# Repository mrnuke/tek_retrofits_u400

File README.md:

# Tektronix U400 channel switch retrofit
Replacement for the Tektronix 155-0236-00 (U400) channel switch hybrid module from 2400 series scopes

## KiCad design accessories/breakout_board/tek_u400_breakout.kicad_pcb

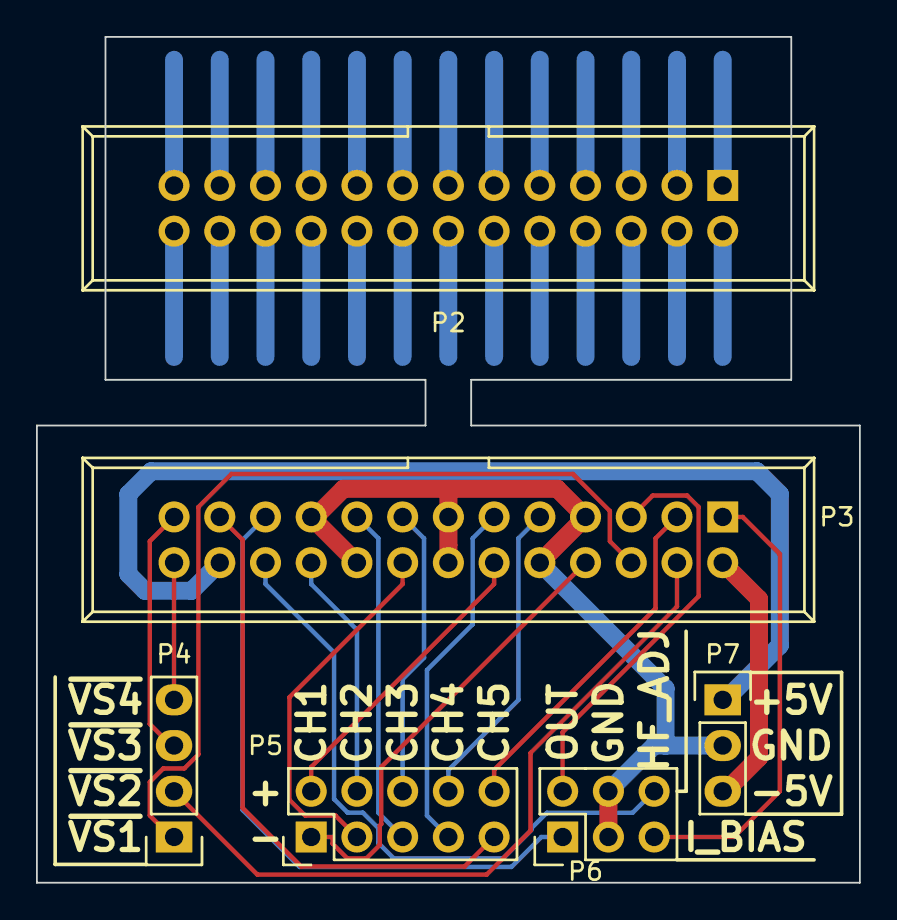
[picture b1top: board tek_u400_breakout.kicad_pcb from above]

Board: 2 copper layers, 45.7 x 47.0 mm, 7 parts (0 on the bottom side), 47 nets.

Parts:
P1: DIL_26_PINS; Tek-DIL-26
P2: CONN_02X13; IDC_Header_Straight_26pins
P3: DIL_26_PINS; IDC_Header_Straight_26pins
P4: CONN_01X04; Pin_Header_Straight_1x04
P5: CONN_02X05; Pin_Header_Straight_2x05
P6: CONN_02X03; Pin_Header_Straight_2x03
P7: CONN_01X03; Pin_Header_Straight_1x03

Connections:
/CH_1+: P3.8, P5.1
/CH_1-: P3.12, P5.2
/CH_2+: P3.16, P5.3
/CH_2-: P3.20, P5.4
/CH_3+: P3.17, P5.5
/CH_3-: P3.15, P5.6
/CH_4+: P3.11, P5.7
/CH_4-: P3.9, P5.8
/CH_5+: P3.23, P5.9
/CH_5-: P3.3, P5.10
/HF_ADJ: P3.22, P6.6
/I_BIAS: P3.1, P6.5
/OUT+: P3.21, P6.1
/OUT-: P3.5, P6.2
/~VS1: P3.6, P4.1
/~VS2: P3.4, P4.2
/~VS3: P3.25, P4.3
/~VS4: P3.26, P4.4
GND: P3.7, P3.10, P3.13, P3.14, P3.18, P3.19, P6.3, P6.4, P7.2
unnamed: P1.1, P2.1
unnamed: P1.2, P2.3
unnamed: P1.3, P2.5
unnamed: P1.4, P2.7
unnamed: P1.5, P2.9
unnamed: P1.6, P2.11
unnamed: P1.7, P2.13
unnamed: P1.8, P2.15
unnamed: P1.9, P2.17
unnamed: P1.10, P2.19
unnamed: P1.11, P2.21
unnamed: P1.12, P2.23
unnamed: P1.13, P2.25
unnamed: P1.14, P2.26
unnamed: P1.15, P2.24
unnamed: P1.16, P2.22
unnamed: P1.17, P2.20
unnamed: P1.18, P2.18
unnamed: P1.19, P2.16
unnamed: P1.20, P2.14
unnamed: P1.21, P2.12
unnamed: P1.22, P2.10
unnamed: P1.23, P2.8
unnamed: P1.24, P2.6
unnamed: P1.25, P2.4
unnamed: P1.26, P2.2
VCC: P3.24, P7.1
VEE: P3.2, P7.3

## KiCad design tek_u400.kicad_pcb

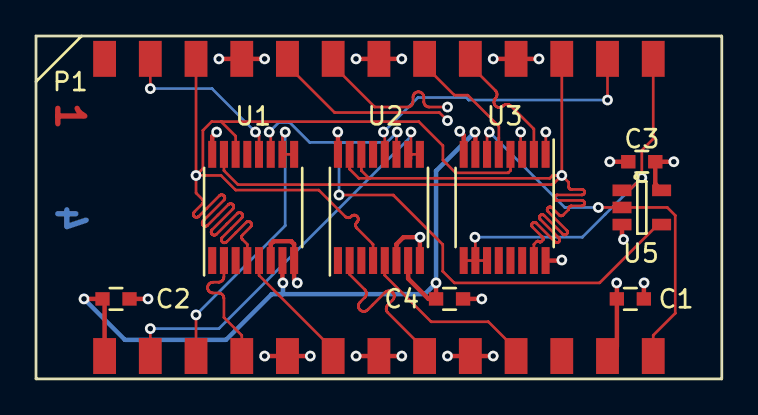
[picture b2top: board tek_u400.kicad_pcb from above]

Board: 4 copper layers, 38.1 x 19.1 mm, 9 parts (1 on the bottom side), 20 nets.

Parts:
C1, C2, C3, C4: C; C_0603
P1: DIL_26_PINS; Tek-DIL-26
U1, U2, U3: DG4053; TSSOP-16_4.4x5mm_Pitch0.65mm
U5: 74AHC1G00; SOT-23-5

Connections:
/CH_1+: P1.23, U1.2
/CH_1-: P1.21, U1.5
/CH_2+: P1.19, U2.2
/CH_2-: P1.17, U2.5
/CH_3+: P1.9, U3.2
/CH_3-: P1.8, U3.5
/CH_4+: P1.6, U3.1
/CH_4-: P1.5, U3.3
/CH_5+: P1.12, U2.12
/CH_5-: P1.2, U1.12
/OUT+: P1.11, U1.15, U2.14, U2.15, U3.15
/OUT-: P1.3, U1.4, U1.14, U2.4, U3.4
/~CH5_SEL: U1.11, U2.11, U5.4
/~VS1: P1.24, U1.9, U1.10
/~VS2: P1.25, U2.9, U2.10
/~VS3: P1.13, U3.9, U3.10, U3.11, U5.1
/~VS4: P1.14, U3.6, U5.2
GND: C1.2, C2.1, C3.2, C4.1, P1.4, P1.7, P1.10, P1.18, P1.20, P1.22, U1.6, U1.8, U2.6, U2.8, U3.8, U5.3
VCC: C1.1, C3.1, P1.15, U1.16, U2.16, U3.16, U5.5
VEE: C2.2, C4.2, P1.26, U1.7, U2.7, U3.7

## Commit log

2016-08-09 Add design for PCB REV A
2016-08-09 Add design for breakout board (initiate hardcore hacking mode)
    The first design (Rev A PCB) does not work as intended, because:
    - Vertical display is squashed (insufficient gain)
    - CH3 does not work. Channel selection truth table was incorrect.
    Because the operational parameters of the original Tek hybrid are not
    all known, hardcore hacking mode is being initiated. These parameters
    must be reverse-enginered. The breakout board added here facilitates
